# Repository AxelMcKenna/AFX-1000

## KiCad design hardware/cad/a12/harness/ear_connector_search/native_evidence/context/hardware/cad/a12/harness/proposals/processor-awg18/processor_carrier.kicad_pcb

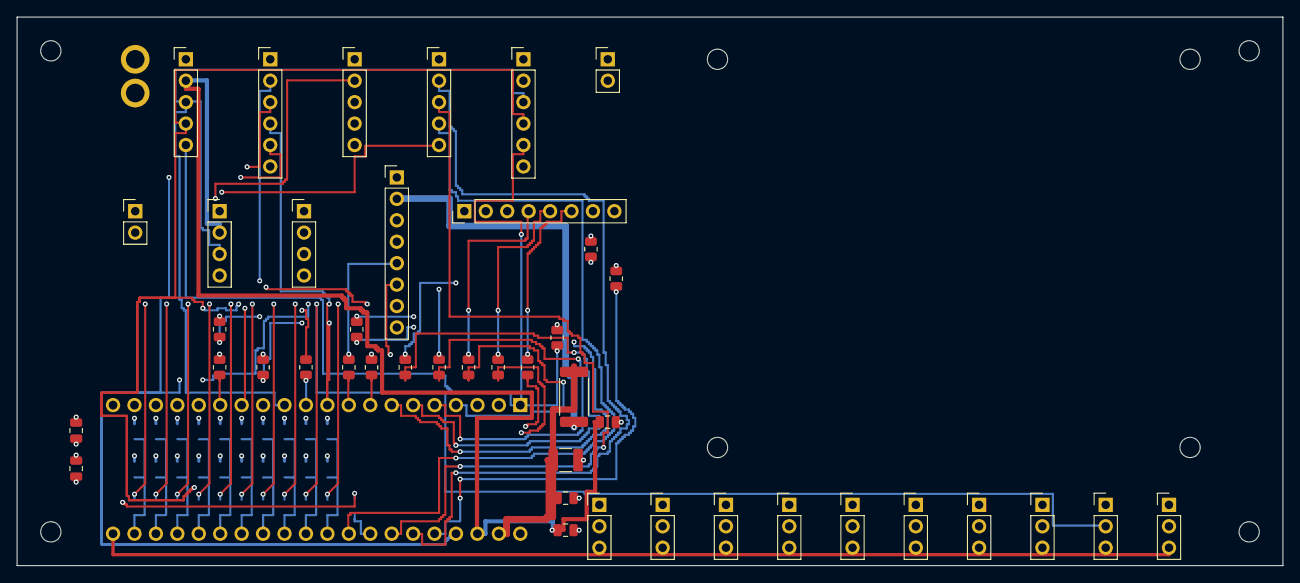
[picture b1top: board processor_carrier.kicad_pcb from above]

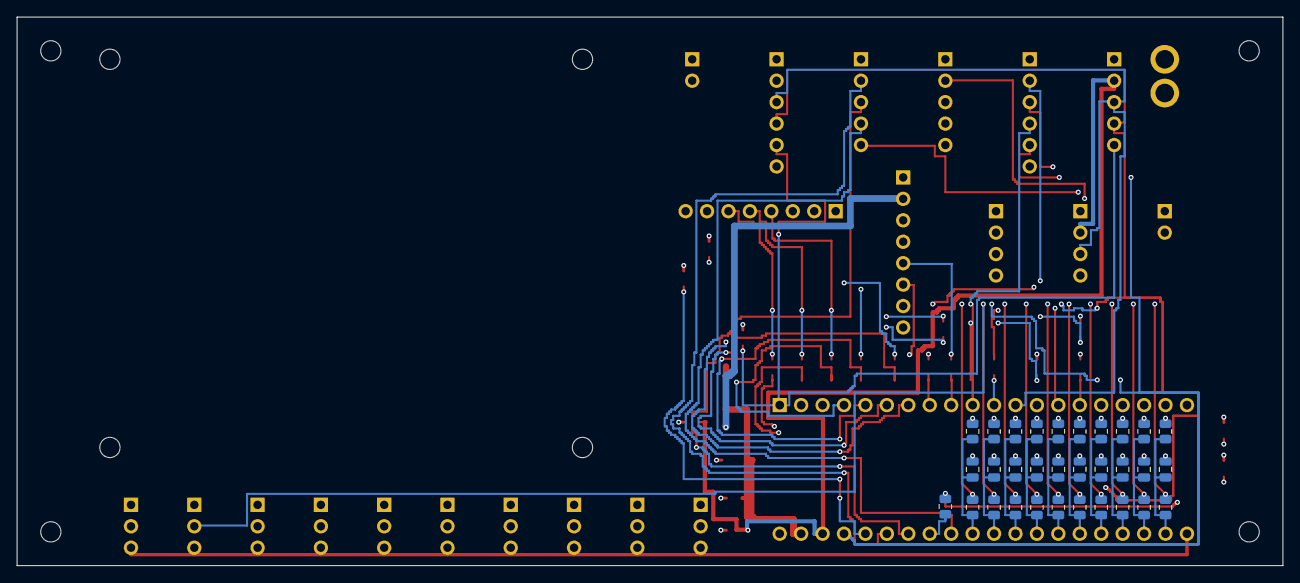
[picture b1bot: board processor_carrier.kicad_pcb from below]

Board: 4 copper layers, 150.0 x 65.0 mm, 84 parts (31 on the bottom side), 61 nets.

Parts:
C1: 22uF 25V X7R; C_1210_3225Metric
C2, C4, C6, C11, C12, C13, C14, C15, C16, C17, C18, C19, C20: 100nF 16V X7R; C_0805_2012Metric
C3: 1uF 16V X7R; C_0805_2012Metric
C5: 4.7uF 16V X7R; C_0805_2012Metric
H1, H2, H3, H4: M2_CLEARANCE; M2_Insert_Clearance
H5, H6, H7, H8: M2_CLEARANCE; M2_Daughter
J1: Alpha6715_AWG18_DIRECT_SOLDER_PROPOSAL; AWG18_Solder_2x1_P4mm_D2p2
J2, J4, J5: Header5; PinHeader_1x05_P2.54mm_Vertical
J3, J6: Header6; PinHeader_1x06_P2.54mm_Vertical
J7, J8: Header2; PinHeader_1x02_P2.54mm_Vertical
J9, J10: Header4; PinHeader_1x04_P2.54mm_Vertical
J11, J12: Header8; PinHeader_1x08_P2.54mm_Vertical
J20, J21, J22, J23, J24, J25, J26, J27, J28, J29: Header3; PinHeader_1x03_P2.54mm_Vertical
R1: 0.47R 1% 1W; R_2512_6332Metric
R2: 10k 1%; R_0805_2012Metric
R3, R4, R5, R6: 100k 1%; R_0805_2012Metric
R10, R11, R12, R13, R14, R15, R16, R17, R18, R19, R20: 33R 1%; R_0805_2012Metric
R31, R32, R33, R34, R35, R36, R37, R38, R39, R40: 1k 1%; R_0805_2012Metric
R41, R42, R43, R44, R45, R46, R47, R48, R49, R50: 1M 1%; R_0805_2012Metric
U1: DaisySeed3; Seed3_Socket40

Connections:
/5V_DIG: J1.1, J11.2, R1.1
/ADC_DATA: J5.4, U1.32
/AGND: C1.2, C2.2, C3.2, C4.2, C5.2, C6.2, C11.2, C12.2, C13.2, C14.2, C15.2, C16.2, C17.2, C18.2, C19.2, C20.2, J1.2, J2.1, J3.1, J4.1, J5.1, J6.1, J7.1, J8.1, J9.1, J10.1, J11.1, J11.8, J12.1, J20.1, J21.1, J22.1, J23.1, J24.1, J25.1, J26.1, J27.1, J28.1, J29.1, R3.2, R4.2, R5.2, R6.2, R41.2, R42.2, R43.2, R44.2, R45.2, R46.2, R47.2, R48.2, R49.2, R50.2, U1.20, U1.40
/ANALOG_OK: J4.4, J6.6
/ARMED: J3.5, R5.1, U1.37
/BCLK: J5.2, U1.35
/BYPASS_SENSE: J3.6, J4.3
/CODEC_RUN: J2.5, J6.5, R6.1, U1.1
/DAC_DATA: J5.5, R14.2
/DAC_DATA_SRC: R14.1, U1.33
/GAIN_REQ: J3.4, R4.1, U1.10
/HEARTBEAT: J3.2, U1.14
/INPUT_READY: J4.5, J7.2
/LED_BLANK: J11.7, R2.1, R13.2
/LED_BLANK_SRC: R13.1, U1.15
/LED_MOSI: J11.4, R12.2
/LED_MOSI_SRC: R12.1, U1.11
/LED_SCK: J11.5, R11.2
/LED_SCK_SRC: R11.1, U1.9
/LED_XLAT: J11.6, R10.2
/LED_XLAT_SRC: R10.1, U1.8
/MCU_PERMIT: J3.3, R3.1, U1.36
/MODE_SEND_RETURN: J4.2, J8.2
/POT_ADC_00: C11.1, R31.2, R41.1, U1.22
/POT_ADC_01: C12.1, R32.2, R42.1, U1.23
/POT_ADC_02: C13.1, R33.2, R43.1, U1.24
/POT_ADC_03: C14.1, R34.2, R44.1, U1.25
/POT_ADC_04: C15.1, R35.2, R45.1, U1.26
/POT_ADC_05: C16.1, R36.2, R46.1, U1.27
/POT_ADC_06: C17.1, R37.2, R47.1, U1.28
/POT_ADC_07: C18.1, R38.2, R48.1, U1.29
/POT_ADC_08: C19.1, R39.2, R49.1, U1.30
/POT_ADC_09: C20.1, R40.2, R50.1, U1.31
/POT_RAW_00: J20.2, R31.1
/POT_RAW_01: J21.2, R32.1
/POT_RAW_02: J22.2, R33.1
/POT_RAW_03: J23.2, R34.1
/POT_RAW_04: J24.2, R35.1
/POT_RAW_05: J25.2, R36.1
/POT_RAW_06: J26.2, R37.1
/POT_RAW_07: J27.2, R38.1
/POT_RAW_08: J28.2, R39.1
/POT_RAW_09: J29.2, R40.1
/SCL: J2.3, J6.3, J9.3, J10.3, U1.12
/SDA: J2.4, J6.4, J9.4, J10.4, U1.13
/SDMMC_CLK: J12.8, R20.2
/SDMMC_CLK_SRC: R20.1, U1.7
/SDMMC_CMD: J12.7, R19.2
/SDMMC_CMD_SRC: R19.1, U1.6
/SDMMC_D0: J12.3, R15.2
/SDMMC_D0_SRC: R15.1, U1.5
/SDMMC_D1: J12.4, R16.2
/SDMMC_D1_SRC: R16.1, U1.4
/SDMMC_D2: J12.5, R17.2
/SDMMC_D2_SRC: R17.1, U1.3
/SDMMC_D3: J12.6, R18.2
/SDMMC_D3_SRC: R18.1, U1.2
/SEED_VIN: C1.1, C2.1, R1.2, U1.39
/V3V3_ANALOG: C3.1, C4.1, J20.3, J21.3, J22.3, J23.3, J24.3, J25.3, J26.3, J27.3, J28.3, J29.3, U1.21
/V3V3_IO: C5.1, C6.1, J2.2, J6.2, J9.2, J10.2, J11.3, J12.2, R2.2, U1.38
/WS: J5.3, U1.34

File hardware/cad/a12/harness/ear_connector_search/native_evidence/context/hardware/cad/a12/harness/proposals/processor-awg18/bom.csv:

Reference,Part_or_value,Footprint,Source,Note
U1,DaisySeed3,RMX_Carrier:Seed3_Socket40,https://daisy.nyc3.cdn.digitaloceanspaces.com/products/seed3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,External firmware profile only. Carrier assembly includes Seed3 and2xSSW-120-02-G-S sockets; clip socket solder tails<=3mm including solder.
J1,Alpha6715_AWG18_DIRECT_SOLDER_PROPOSAL,RMX_Carrier:AWG18_Solder_2x1_P4mm_D2p2,https://www.alphawire.com/products/wire/ecogen/ecowire/6715,"Separate direct-solder geometry proposal; max pretinned OD1.4mm, finished bores2.1..2.3mm, solder/strain/current/life unqualified"
J2,Header5,Connector_PinHeader_2.54mm:PinHeader_1x05_P2.54mm_Vertical,,E18 J5; CODEC_RUN alias CONTROL_RESET_N; external profile only.
J3,Header6,Connector_PinHeader_2.54mm:PinHeader_1x06_P2.54mm_Vertical,,E11 J2 six-pin order; bypass sense passes to E18 rear header.
J4,Header5,Connector_PinHeader_2.54mm:PinHeader_1x05_P2.54mm_Vertical,,E18 J4; BYPASS_SENSE alias MANUAL_BYPASS.
J5,Header5,Connector_PinHeader_2.54mm:PinHeader_1x05_P2.54mm_Vertical,,E09 J3; DAC_DATA source damping at carrier.
J6,Header6,Connector_PinHeader_2.54mm:PinHeader_1x06_P2.54mm_Vertical,,Split harness to E09 J4 IO power/J5 bus/status. Do not join independent3.3V outputs.
J7,Header2,Connector_PinHeader_2.54mm:PinHeader_1x02_P2.54mm_Vertical,,E11 J6 status.
J8,Header2,Connector_PinHeader_2.54mm:PinHeader_1x02_P2.54mm_Vertical,,Rear maintained CONNECTION contact: closed=send/return.
J9,Header4,Connector_PinHeader_2.54mm:PinHeader_1x04_P2.54mm_Vertical,,Trill Craft bus; include module pull-ups in whole-bus budget.
J10,Header4,Connector_PinHeader_2.54mm:PinHeader_1x04_P2.54mm_Vertical,,AS5600 board bus; sensor board incomplete.
J11,Header8,Connector_PinHeader_2.54mm:PinHeader_1x08_P2.54mm_Vertical,,TLC5947 board interface; receiving BLANK pull-up still required on future LED board.
J12,Header8,Connector_PinHeader_2.54mm:PinHeader_1x08_P2.54mm_Vertical,,"Reserved SDMMC interface. Card-power budget, socket/detect, filesystem and physical SI unfinished."
R1,0.47R 1% 1W,Resistor_SMD:R_2512_6332Metric,,"Source resistor budget uses0.5A; physical load, thermal and startup qualification open."
R2,10k 1%,Resistor_SMD:R_0805_2012Metric,,
R3,100k 1%,Resistor_SMD:R_0805_2012Metric,,
R4,100k 1%,Resistor_SMD:R_0805_2012Metric,,
R5,100k 1%,Resistor_SMD:R_0805_2012Metric,,
R6,100k 1%,Resistor_SMD:R_0805_2012Metric,,
R10,33R 1%,Resistor_SMD:R_0805_2012Metric,,Source damping; physical edge/SI qualification unfinished.
R11,33R 1%,Resistor_SMD:R_0805_2012Metric,,Source damping; physical edge/SI qualification unfinished.
R12,33R 1%,Resistor_SMD:R_0805_2012Metric,,Source damping; physical edge/SI qualification unfinished.
R13,33R 1%,Resistor_SMD:R_0805_2012Metric,,Source damping; physical edge/SI qualification unfinished.
R14,33R 1%,Resistor_SMD:R_0805_2012Metric,,Source damping; physical edge/SI qualification unfinished.
R15,33R 1%,Resistor_SMD:R_0805_2012Metric,,Source damping; physical edge/SI qualification unfinished.
R16,33R 1%,Resistor_SMD:R_0805_2012Metric,,Source damping; physical edge/SI qualification unfinished.
R17,33R 1%,Resistor_SMD:R_0805_2012Metric,,Source damping; physical edge/SI qualification unfinished.
R18,33R 1%,Resistor_SMD:R_0805_2012Metric,,Source damping; physical edge/SI qualification unfinished.
R19,33R 1%,Resistor_SMD:R_0805_2012Metric,,Source damping; physical edge/SI qualification unfinished.
R20,33R 1%,Resistor_SMD:R_0805_2012Metric,,Source damping; physical edge/SI qualification unfinished.
C1,22uF 25V X7R,Capacitor_SMD:C_1210_3225Metric,,
C2,100nF 16V X7R,Capacitor_SMD:C_0805_2012Metric,,
C3,1uF 16V X7R,Capacitor_SMD:C_0805_2012Metric,,
C4,100nF 16V X7R,Capacitor_SMD:C_0805_2012Metric,,
C5,4.7uF 16V X7R,Capacitor_SMD:C_0805_2012Metric,,
C6,100nF 16V X7R,Capacitor_SMD:C_0805_2012Metric,,
J20,Header3,Connector_PinHeader_2.54mm:PinHeader_1x03_P2.54mm_Vertical,,input: 10k linear pot; excitation is module analog3.3V output.
R31,1k 1%,Resistor_SMD:R_0805_2012Metric,,
C11,100nF 16V X7R,Capacitor_SMD:C_0805_2012Metric,,
R41,1M 1%,Resistor_SMD:R_0805_2012Metric,,Open-wiper bleed; does not provide wire-fault detection.
J21,Header3,Connector_PinHeader_2.54mm:PinHeader_1x03_P2.54mm_Vertical,,output: 10k linear pot; excitation is module analog3.3V output.
R32,1k 1%,Resistor_SMD:R_0805_2012Metric,,
C12,100nF 16V X7R,Capacitor_SMD:C_0805_2012Metric,,
R42,1M 1%,Resistor_SMD:R_0805_2012Metric,,Open-wiper bleed; does not provide wire-fault detection.
J22,Header3,Connector_PinHeader_2.54mm:PinHeader_1x03_P2.54mm_Vertical,,low: 10k linear pot; excitation is module analog3.3V output.
R33,1k 1%,Resistor_SMD:R_0805_2012Metric,,
C13,100nF 16V X7R,Capacitor_SMD:C_0805_2012Metric,,
R43,1M 1%,Resistor_SMD:R_0805_2012Metric,,Open-wiper bleed; does not provide wire-fault detection.
J23,Header3,Connector_PinHeader_2.54mm:PinHeader_1x03_P2.54mm_Vertical,,mid: 10k linear pot; excitation is module analog3.3V output.
R34,1k 1%,Resistor_SMD:R_0805_2012Metric,,
C14,100nF 16V X7R,Capacitor_SMD:C_0805_2012Metric,,
R44,1M 1%,Resistor_SMD:R_0805_2012Metric,,Open-wiper bleed; does not provide wire-fault detection.
J24,Header3,Connector_PinHeader_2.54mm:PinHeader_1x03_P2.54mm_Vertical,,high: 10k linear pot; excitation is module analog3.3V output.
R35,1k 1%,Resistor_SMD:R_0805_2012Metric,,
C15,100nF 16V X7R,Capacitor_SMD:C_0805_2012Metric,,
R45,1M 1%,Resistor_SMD:R_0805_2012Metric,,Open-wiper bleed; does not provide wire-fault detection.
J25,Header3,Connector_PinHeader_2.54mm:PinHeader_1x03_P2.54mm_Vertical,,scene_depth: 10k linear pot; excitation is module analog3.3V output.
R36,1k 1%,Resistor_SMD:R_0805_2012Metric,,
C16,100nF 16V X7R,Capacitor_SMD:C_0805_2012Metric,,
R46,1M 1%,Resistor_SMD:R_0805_2012Metric,,Open-wiper bleed; does not provide wire-fault detection.
J26,Header3,Connector_PinHeader_2.54mm:PinHeader_1x03_P2.54mm_Vertical,,x_level: 10k linear pot; excitation is module analog3.3V output.
R37,1k 1%,Resistor_SMD:R_0805_2012Metric,,
C17,100nF 16V X7R,Capacitor_SMD:C_0805_2012Metric,,
R47,1M 1%,Resistor_SMD:R_0805_2012Metric,,Open-wiper bleed; does not provide wire-fault detection.
J27,Header3,Connector_PinHeader_2.54mm:PinHeader_1x03_P2.54mm_Vertical,,x_pitch: 10k linear pot; excitation is module analog3.3V output.
R38,1k 1%,Resistor_SMD:R_0805_2012Metric,,
C18,100nF 16V X7R,Capacitor_SMD:C_0805_2012Metric,,
R48,1M 1%,Resistor_SMD:R_0805_2012Metric,,Open-wiper bleed; does not provide wire-fault detection.
J28,Header3,Connector_PinHeader_2.54mm:PinHeader_1x03_P2.54mm_Vertical,,scene_time: 10k linear pot; excitation is module analog3.3V output.
R39,1k 1%,Resistor_SMD:R_0805_2012Metric,,
C19,100nF 16V X7R,Capacitor_SMD:C_0805_2012Metric,,
R49,1M 1%,Resistor_SMD:R_0805_2012Metric,,Open-wiper bleed; does not provide wire-fault detection.
J29,Header3,Connector_PinHeader_2.54mm:PinHeader_1x03_P2.54mm_Vertical,,scene_resonance: 10k linear pot; excitation is module analog3.3V output.
R40,1k 1%,Resistor_SMD:R_0805_2012Metric,,
C20,100nF 16V X7R,Capacitor_SMD:C_0805_2012Metric,,
R50,1M 1%,Resistor_SMD:R_0805_2012Metric,,Open-wiper bleed; does not provide wire-fault detection.
